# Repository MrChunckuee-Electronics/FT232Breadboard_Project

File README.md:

# FT232_Breadboard

***
Puedes seguirme en:
- [Blogspot](http://mrchunckuee.blogspot.com)
- [Instagram](https://www.instagram.com/mrchunckuee_electronics/)
- [Facebook](https://www.facebook.com/MrChunckueeElectronics)
- [Twitter](https://twitter.com/MrChunckuee)
- [YouTube](https://www.youtube.com/@MrChunckueeElectronics)

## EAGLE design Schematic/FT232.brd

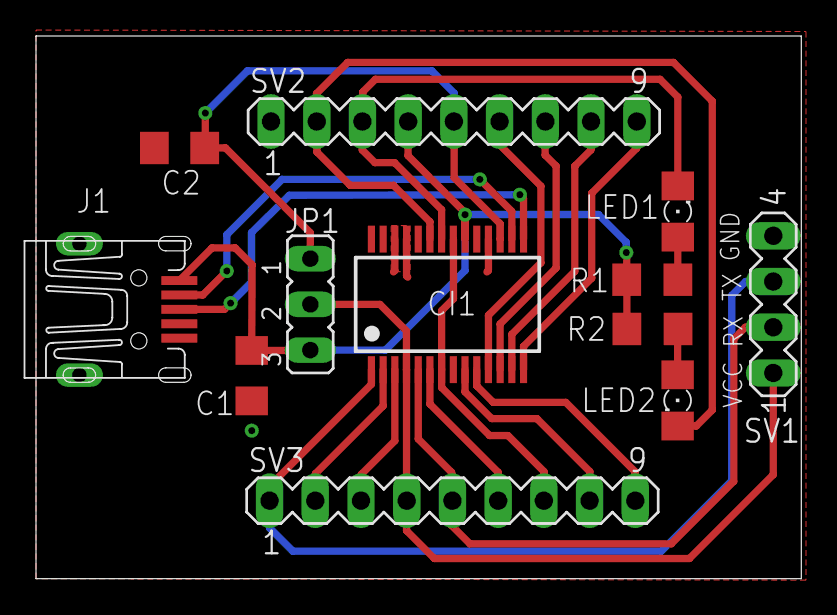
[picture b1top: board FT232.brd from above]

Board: 2 copper layers, 42.5 x 30.1 mm, 12 parts (0 on the bottom side), 21 nets.

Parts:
C1, C2: 0.1uF; C1206
CI1: FT232RL; SSOP28
J1: UX60-MB-5S8
JP1: JP2
LED1: BLUE; 1206
LED2: RED; 1206
R1, R2: 1k; R1206
SV1: MA04-1
SV2, SV3: MA09-1

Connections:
+3V3: C2.1, CI1.17, JP1.1, SV2.5
+5V: C1.1, CI1.20, J1.VCC, JP1.3, R1.2, R2.2, SV2.4
CBUS0/TXLED: CI1.23, LED2.C, SV2.2
CBUS1/RXLED: CI1.22, LED1.C, SV2.3
CBUS2/TXDEN: CI1.13, SV2.8
CBUS3/PWREN: CI1.14, SV2.9
CBUS4/SLEEP: CI1.12, SV2.7
CTS: CI1.11, SV2.6
DCD: CI1.10, SV3.9
DSR: CI1.9, SV3.8
DTR: CI1.2, SV3.2
GND: C1.2, C2.2, CI1.7, CI1.18, CI1.21, CI1.25, CI1.26, J1.GND, SV1.4, SV2.1, SV3.7
unnamed: LED1.A, R1.1
unnamed: LED2.A, R2.1
unnamed: CI1.16, J1.D-
unnamed: CI1.15, J1.D+
RI: CI1.6, SV3.6
RTS: CI1.3, SV3.3
RXD: CI1.5, SV1.2, SV3.5
TXD: CI1.1, SV1.3, SV3.1
VCCIO: CI1.4, JP1.2, SV1.1, SV3.4

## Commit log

2017-09-26 FT232_Breadboard
